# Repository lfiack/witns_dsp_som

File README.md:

# DSP System on Module from WITNS

## Make the project work
This project uses a submodule for the KiCAD library. To get it properly, use the `--recursive` option when cloning the repo :

```bash
git clone --recursive git@github.com:lfiack/witns_dsp_som
```

If you forgot the `--recursive` option (as I do quite often), you can type the following command :

```bash
git submodule update --init --recursive
```

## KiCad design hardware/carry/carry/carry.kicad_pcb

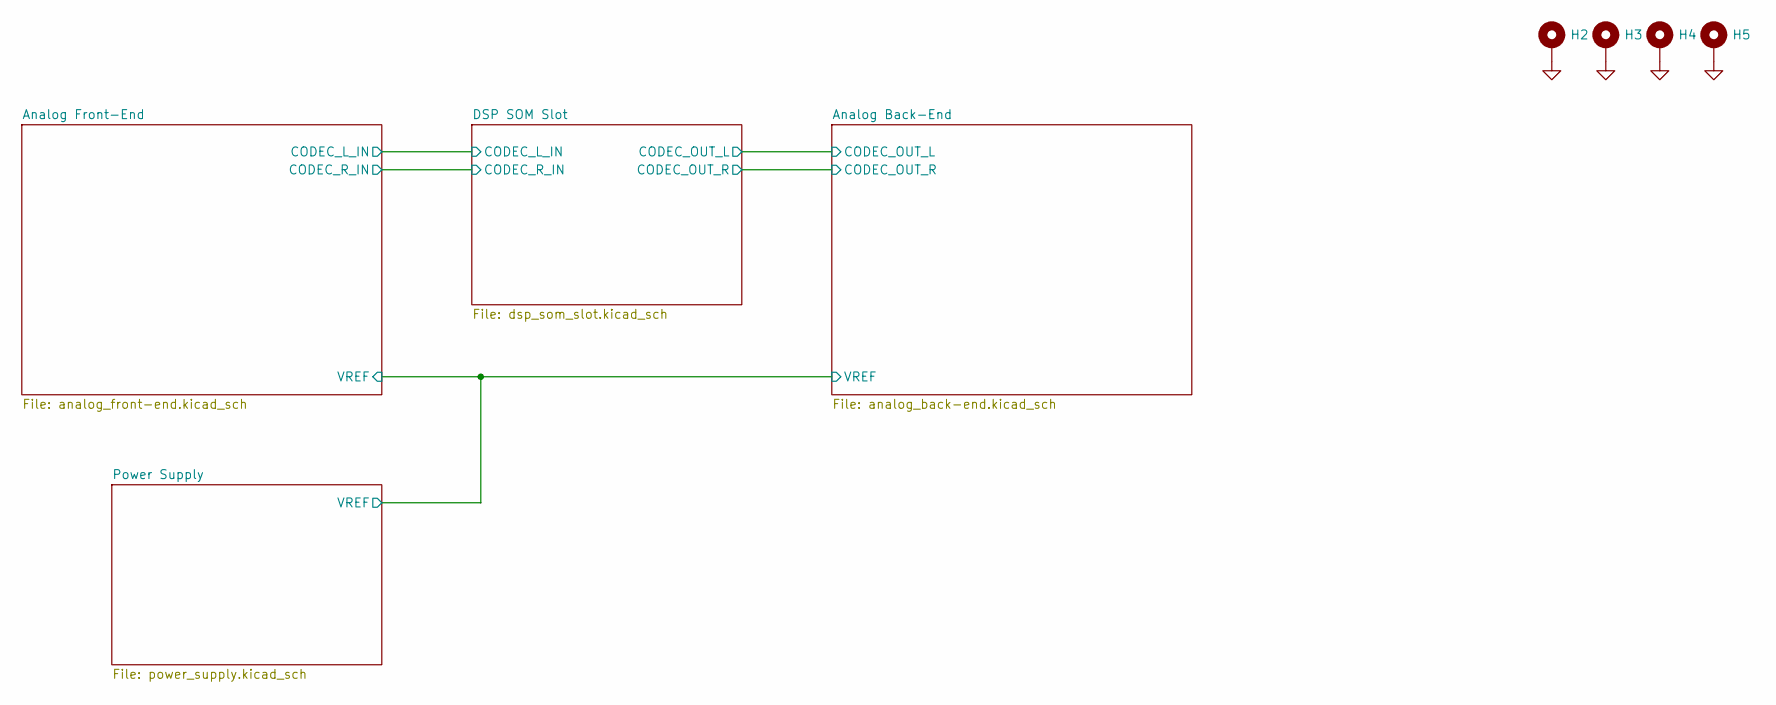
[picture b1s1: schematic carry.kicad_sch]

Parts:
H2, H3, H4, H5: MountingHole_Pad; MountingHole_3.2mm_M3_Pad_Via

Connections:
GND: H2.1, H3.1, H4.1, H5.1; also elsewhere on the board

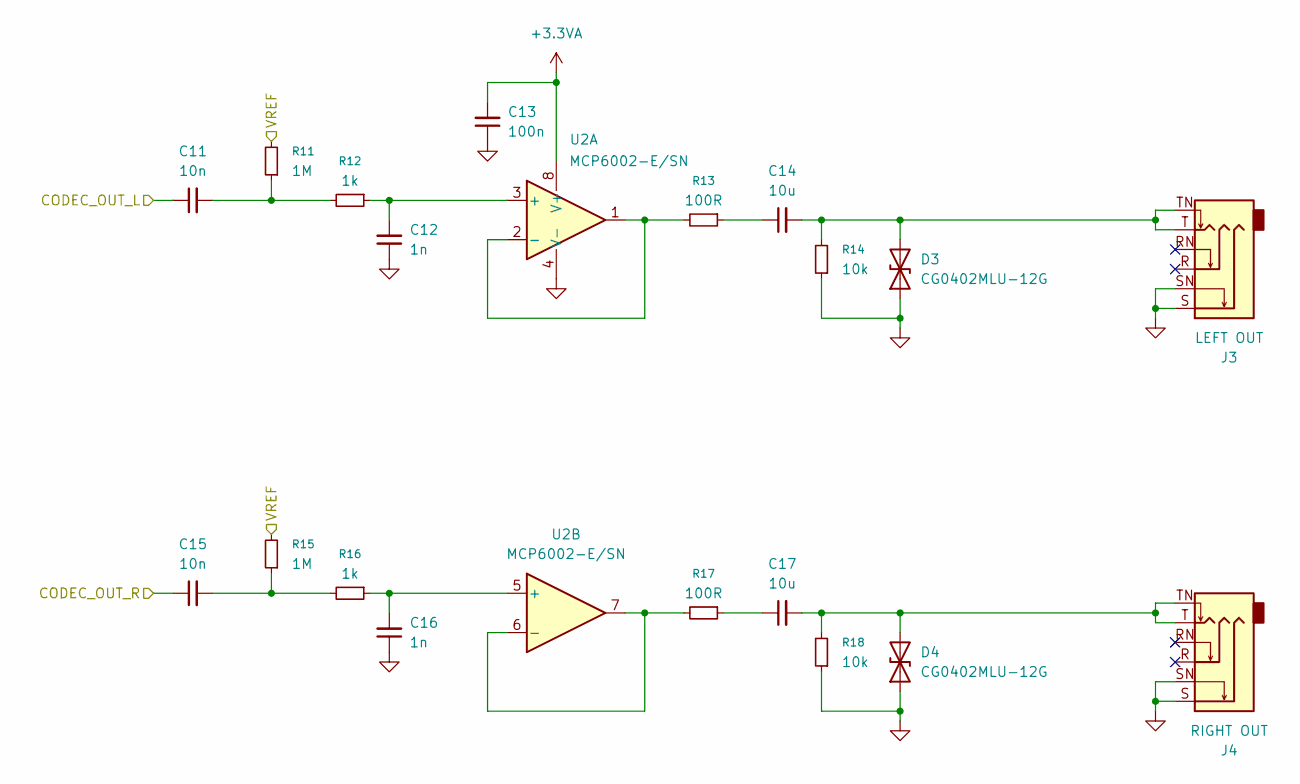
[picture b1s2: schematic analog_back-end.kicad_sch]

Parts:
C11, C15: 10n; C_0603_1608Metric
C12, C16: 1n; C_0603_1608Metric
C13: 100n; C_0603_1608Metric
C14, C17: 10u; C_0603_1608Metric
D3, D4: CG0402MLU-12G; D_0402_1005Metric
J3: LEFT OUT; Jack_6.35mm_Neutrik_NMJ6HCD3_Horizontal
J4: RIGHT OUT; Jack_6.35mm_Neutrik_NMJ6HCD3_Horizontal
R11, R15: 1M; R_0603_1608Metric
R12, R16: 1k; R_0603_1608Metric
R13, R17: 100R; R_0603_1608Metric
R14, R18: 10k; R_0603_1608Metric
U2: MCP6002-E/SN; SOIC-8_3.9x4.9mm_P1.27mm

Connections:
+3.3VA: C13.2, U2.8 (V+); also elsewhere on the board
/Analog Back-End/CODEC_OUT_L: C11.1; also elsewhere on the board
/Analog Back-End/CODEC_OUT_R: C15.1; also elsewhere on the board
/Analog Back-End/VREF: R11.2, R15.2; also elsewhere on the board
GND: C12.1, C13.1, C16.1, D3.1 (A1), D4.1 (A1), J3.S, J3.SN, J4.S, J4.SN, R14.1, R18.1, U2.4 (V-); also elsewhere on the board
unnamed: C11.2, R11.1, R12.2
unnamed: C14.1, R13.1
unnamed: C15.2, R15.1, R16.2
unnamed: C17.1, R17.1
unnamed: C14.2, D3.2 (A2), J3.T, J3.TN, R14.2
unnamed: C17.2, D4.2 (A2), J4.T, J4.TN, R18.2
unnamed: C12.2, R12.1, U2.3 (+)
unnamed: R13.2, U2.1, U2.2 (-)
unnamed: C16.2, R16.1, U2.5 (+)
unnamed: R17.2, U2.6 (-), U2.7

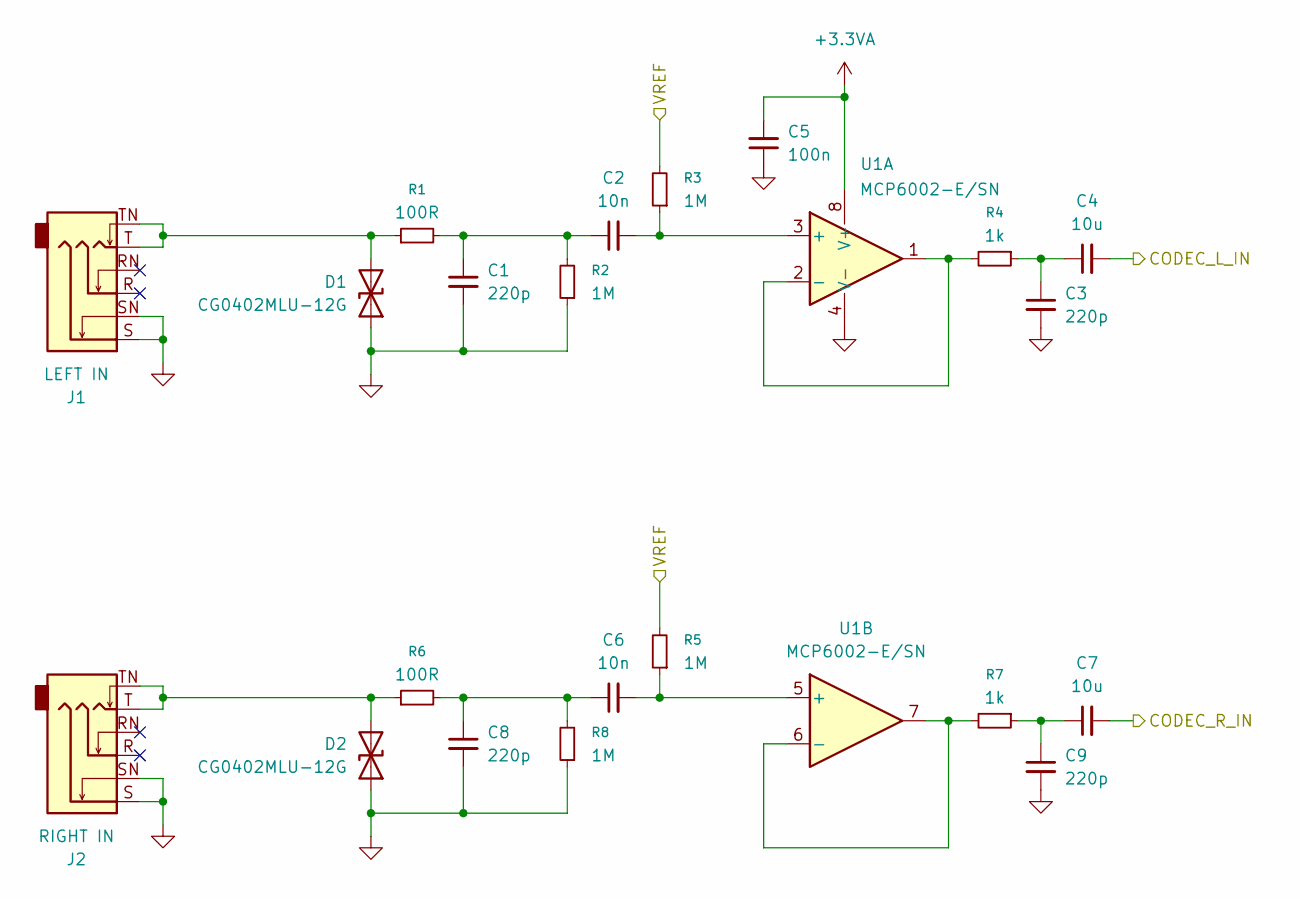
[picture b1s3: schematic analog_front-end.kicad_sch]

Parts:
C1, C3, C8, C9: 220p; C_0603_1608Metric
C2, C6: 10n; C_0603_1608Metric
C4, C7: 10u; C_0603_1608Metric
C5: 100n; C_0603_1608Metric
D1, D2: CG0402MLU-12G; D_0402_1005Metric
J1: LEFT IN; Jack_6.35mm_Neutrik_NMJ6HCD3_Horizontal
J2: RIGHT IN; Jack_6.35mm_Neutrik_NMJ6HCD3_Horizontal
R1, R6: 100R; R_0603_1608Metric
R2, R3, R5, R8: 1M; R_0603_1608Metric
R4, R7: 1k; R_0603_1608Metric
U1: MCP6002-E/SN; SOIC-8_3.9x4.9mm_P1.27mm

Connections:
+3.3VA: C5.2, U1.8 (V+); also elsewhere on the board
/Analog Back-End/VREF: R3.2, R5.2; also elsewhere on the board
/Analog Front-End/CODEC_L_IN: C4.2; also elsewhere on the board
/Analog Front-End/CODEC_R_IN: C7.2; also elsewhere on the board
GND: C1.2, C3.2, C5.1, C8.2, C9.2, D1.1 (A1), D2.1 (A1), J1.S, J1.SN, J2.S, J2.SN, R2.1, R8.1, U1.4 (V-); also elsewhere on the board
unnamed: C1.1, C2.1, R1.2, R2.2
unnamed: C3.1, C4.1, R4.1
unnamed: C6.1, C8.1, R6.2, R8.2
unnamed: C7.1, C9.1, R7.1
unnamed: D1.2 (A2), J1.T, J1.TN, R1.1
unnamed: D2.2 (A2), J2.T, J2.TN, R6.1
unnamed: C2.2, R3.1, U1.3 (+)
unnamed: R4.2, U1.1, U1.2 (-)
unnamed: C6.2, R5.1, U1.5 (+)
unnamed: R7.2, U1.6 (-), U1.7

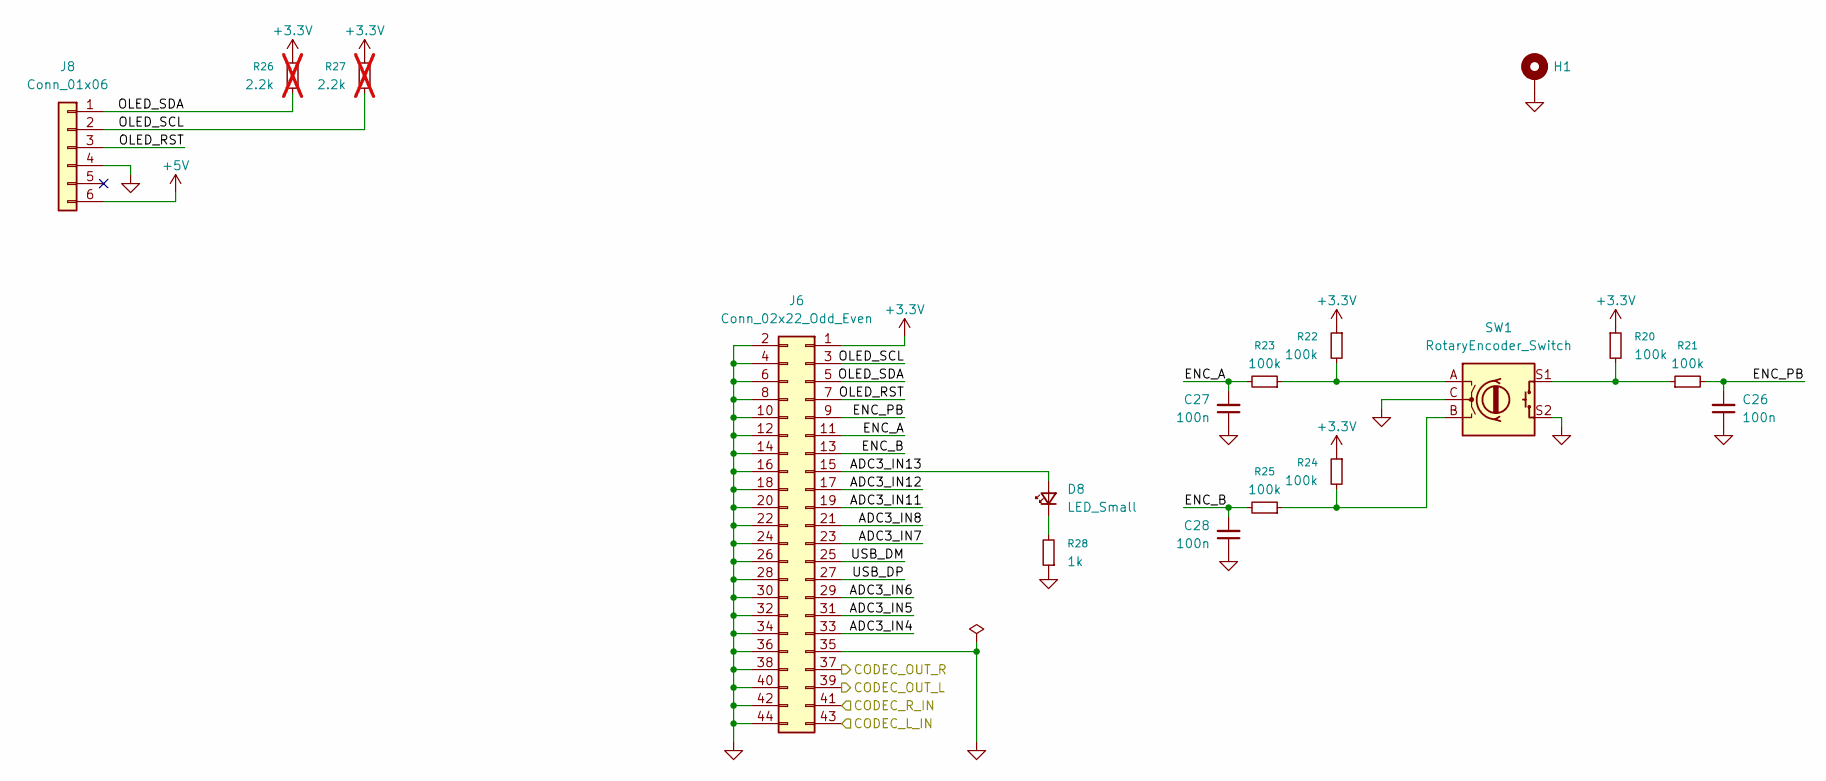
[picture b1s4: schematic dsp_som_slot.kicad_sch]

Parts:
C26, C27, C28: 100n; C_0603_1608Metric
D8: LED_Small; LED_0603_1608Metric
H1: MountingHole_Pad; MountingHole_3.2mm_M3_Pad_Via
J6: Conn_02x22_Odd_Even; PinSocket_2x22_P2.54mm_Vertical
J8: Conn_01x06; PinSocket_1x06_P2.54mm_Vertical
R20, R21, R22, R23, R24, R25: 100k; R_0603_1608Metric
R26, R27: 2.2k; R_0603_1608Metric; not fitted
R28: 1k; R_0603_1608Metric
SW1: RotaryEncoder_Switch; RotaryEncoder_Alps_EC12E-Switch_Vertical_H20mm_CircularMoun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

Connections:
+3.3V: J6.1, R20.1, R22.1, R24.1, R26.1, R27.1; also elsewhere on the board
+5V: J8.6; also elsewhere on the board
/Analog Back-End/CODEC_OUT_L: J6.39; also elsewhere on the board
/Analog Back-End/CODEC_OUT_R: J6.37; also elsewhere on the board
/Analog Front-End/CODEC_L_IN: J6.43; also elsewhere on the board
/Analog Front-End/CODEC_R_IN: J6.41; also elsewhere on the board
/DSP SOM Slot/ADC3_IN4: J6.33
/DSP SOM Slot/ADC3_IN5: J6.31
/DSP SOM Slot/ADC3_IN6: J6.29
/DSP SOM Slot/ADC3_IN7: J6.23
/DSP SOM Slot/ADC3_IN8: J6.21
/DSP SOM Slot/ADC3_IN11: J6.19
/DSP SOM Slot/ADC3_IN12: J6.17
/DSP SOM Slot/ADC3_IN13: D8.2 (A), J6.15
/DSP SOM Slot/ENC_A: C27.2, J6.11, R23.2
/DSP SOM Slot/ENC_B: C28.2, J6.13, R25.2
/DSP SOM Slot/ENC_PB: C26.2, J6.9, R21.2
/DSP SOM Slot/OLED_RST: J6.7, J8.3
/DSP SOM Slot/OLED_SCL: J6.3, J8.2, R27.2
/DSP SOM Slot/OLED_SDA: J6.5, J8.1, R26.2
/DSP SOM Slot/USB_DM: J6.25
/DSP SOM Slot/USB_DP: J6.27
GND: C26.1, C27.1, C28.1, H1.1, J6.2, J6.4, J6.6, J6.8, J6.10, J6.12, J6.14, J6.16, J6.18, J6.20, J6.22, J6.24, J6.26, J6.28, J6.30, J6.32, J6.34, J6.35, J6.36, J6.38, J6.40, J6.42, J6.44, J8.4, R28.1, SW1.C, SW1.S2; also elsewhere on the board
unnamed: D8.1 (K), R28.2
unnamed: R20.2, R21.1, SW1.S1
unnamed: R22.2, R23.1, SW1.A
unnamed: R24.2, R25.1, SW1.B

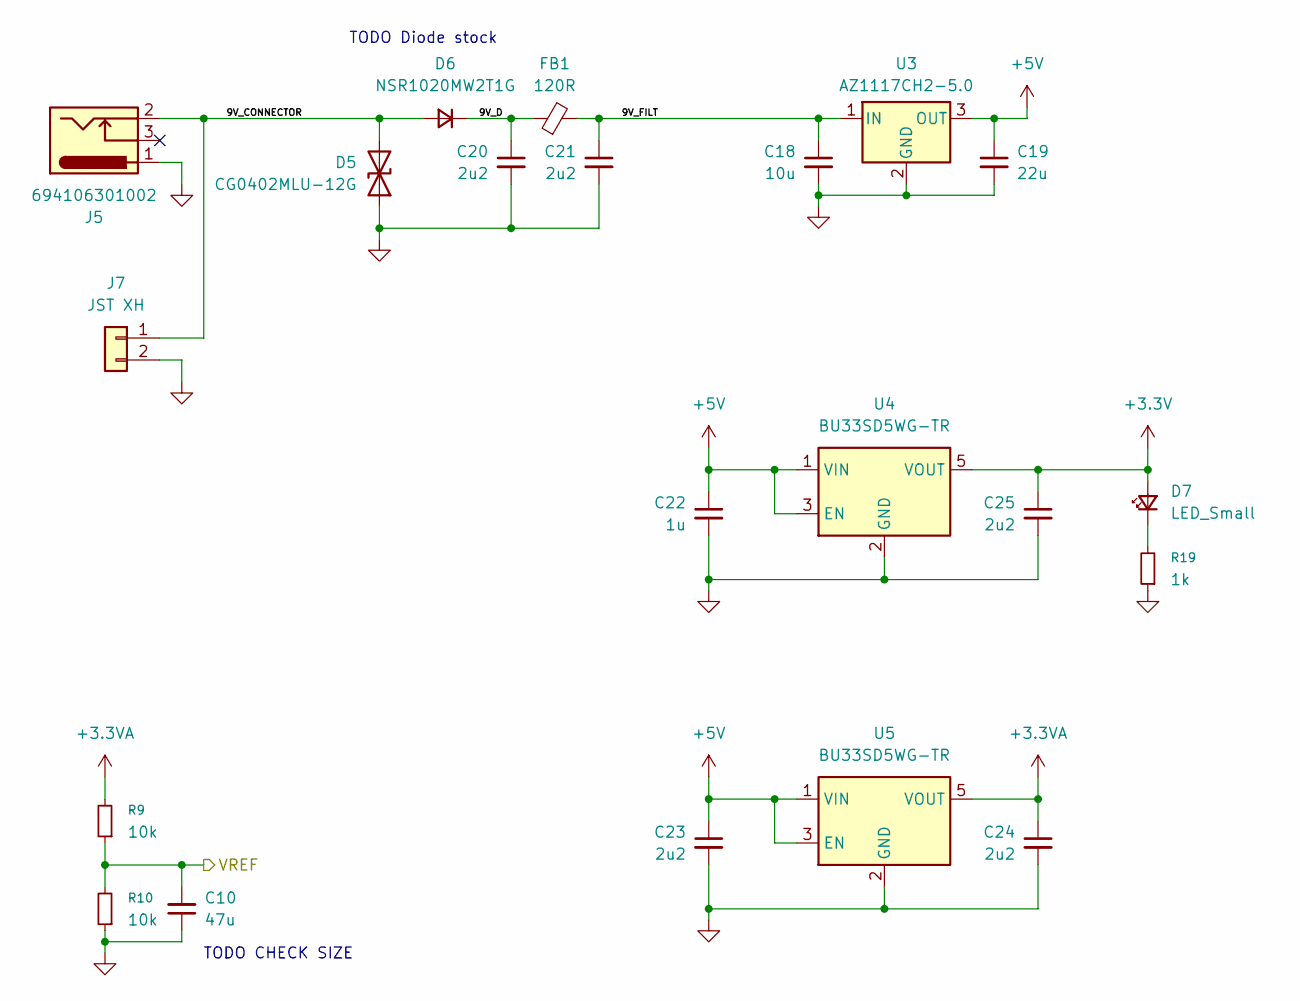
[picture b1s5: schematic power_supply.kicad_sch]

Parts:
C10: 47u; C_0603_1608Metric
C18: 10u; C_0805_2012Metric
C19: 22u; C_0805_2012Metric
C20, C21, C23, C24, C25: 2u2; C_0603_1608Metric
C22: 1u; C_0603_1608Metric
D5: CG0402MLU-12G; D_0402_1005Metric
D6: NSR1020MW2T1G; D_SOD-323
D7: LED_Small; LED_0603_1608Metric
FB1: 120R; L_0603_1608Metric
J5: 694106301002; BarrelJack_Wuerth_6941xx301002
J7: JST XH; JST_XH_B2B-XH-A_1x02_P2.50mm_Vertical
R9, R10: 10k; R_0603_1608Metric
R19: 1k; R_0603_1608Metric
U3: AZ1117CH2-5.0; SOT-223-3_TabPin2
U4, U5: BU33SD5WG-TR; SOT-23-5

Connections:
+3.3V: C25.1, D7.2 (A), U4.5 (VOUT); also elsewhere on the board
+3.3VA: C24.1, R9.2, U5.5 (VOUT); also elsewhere on the board
+5V: C19.1, C22.1, C23.1, U3.3 (OUT), U4.1 (VIN), U4.3 (EN), U5.1 (VIN), U5.3 (EN); also elsewhere on the board
/Analog Back-End/VREF: C10.2, R9.1, R10.2; also elsewhere on the board
/Power Supply/9V_CONNECTOR: D5.2 (A2), D6.2 (A), J5.2, J7.1
/Power Supply/9V_D: C20.1, D6.1 (K), FB1.1
/Power Supply/9V_FILT: C18.1, C21.1, FB1.2, U3.1 (IN)
GND: C10.1, C18.2, C19.2, C20.2, C21.2, C22.2, C23.2, C24.2, C25.2, D5.1 (A1), J5.1, J7.2, R10.1, R19.1, U3.2 (GND), U4.2 (GND), U5.2 (GND); also elsewhere on the board
unnamed: D7.1 (K), R19.2

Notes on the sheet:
TODO Diode stock
TODO CHECK SIZE

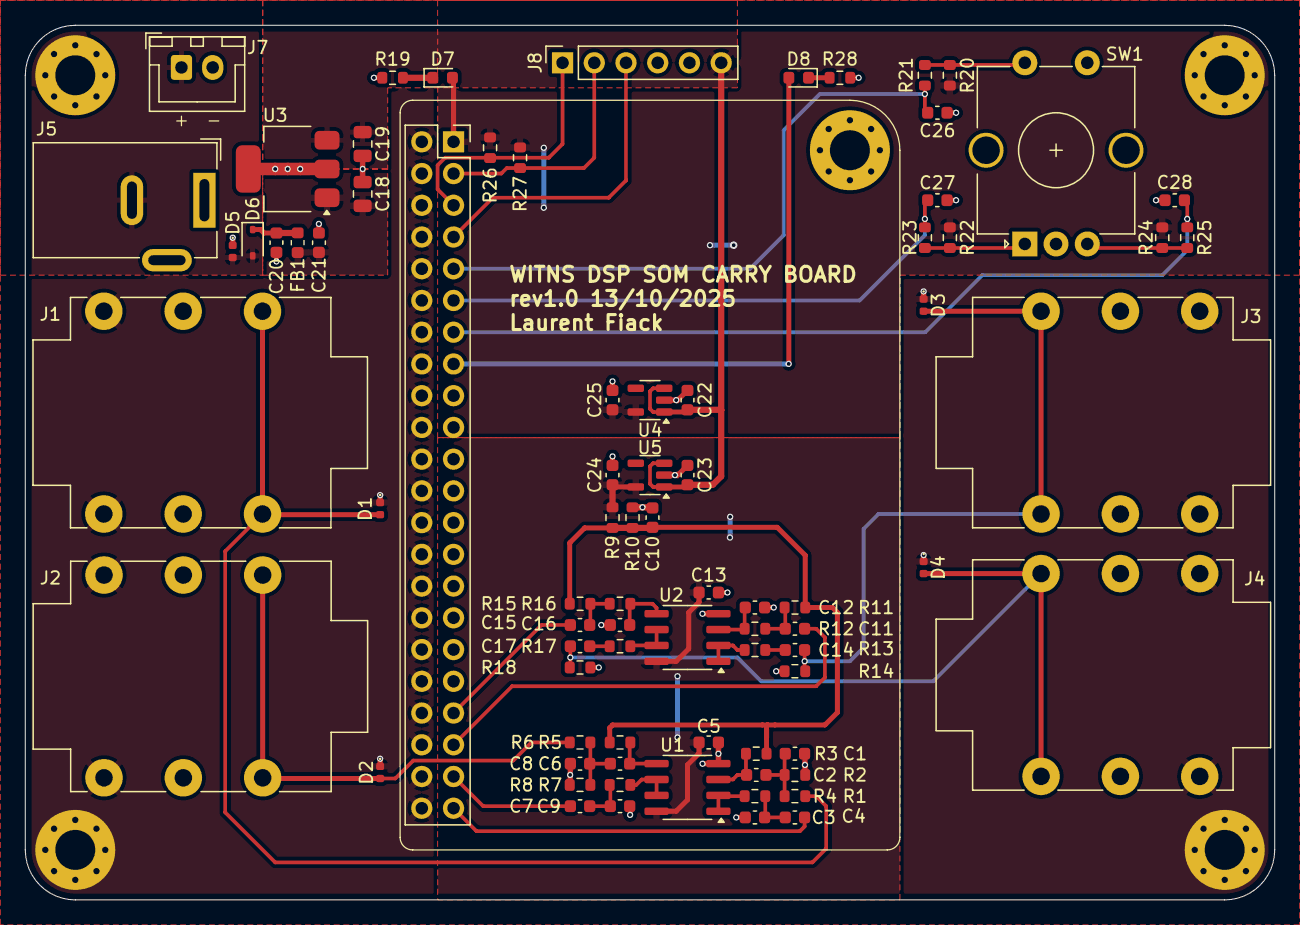
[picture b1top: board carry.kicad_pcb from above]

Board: 2 copper layers, 100.0 x 70.0 mm, 84 parts (0 on the bottom side), 44 nets.

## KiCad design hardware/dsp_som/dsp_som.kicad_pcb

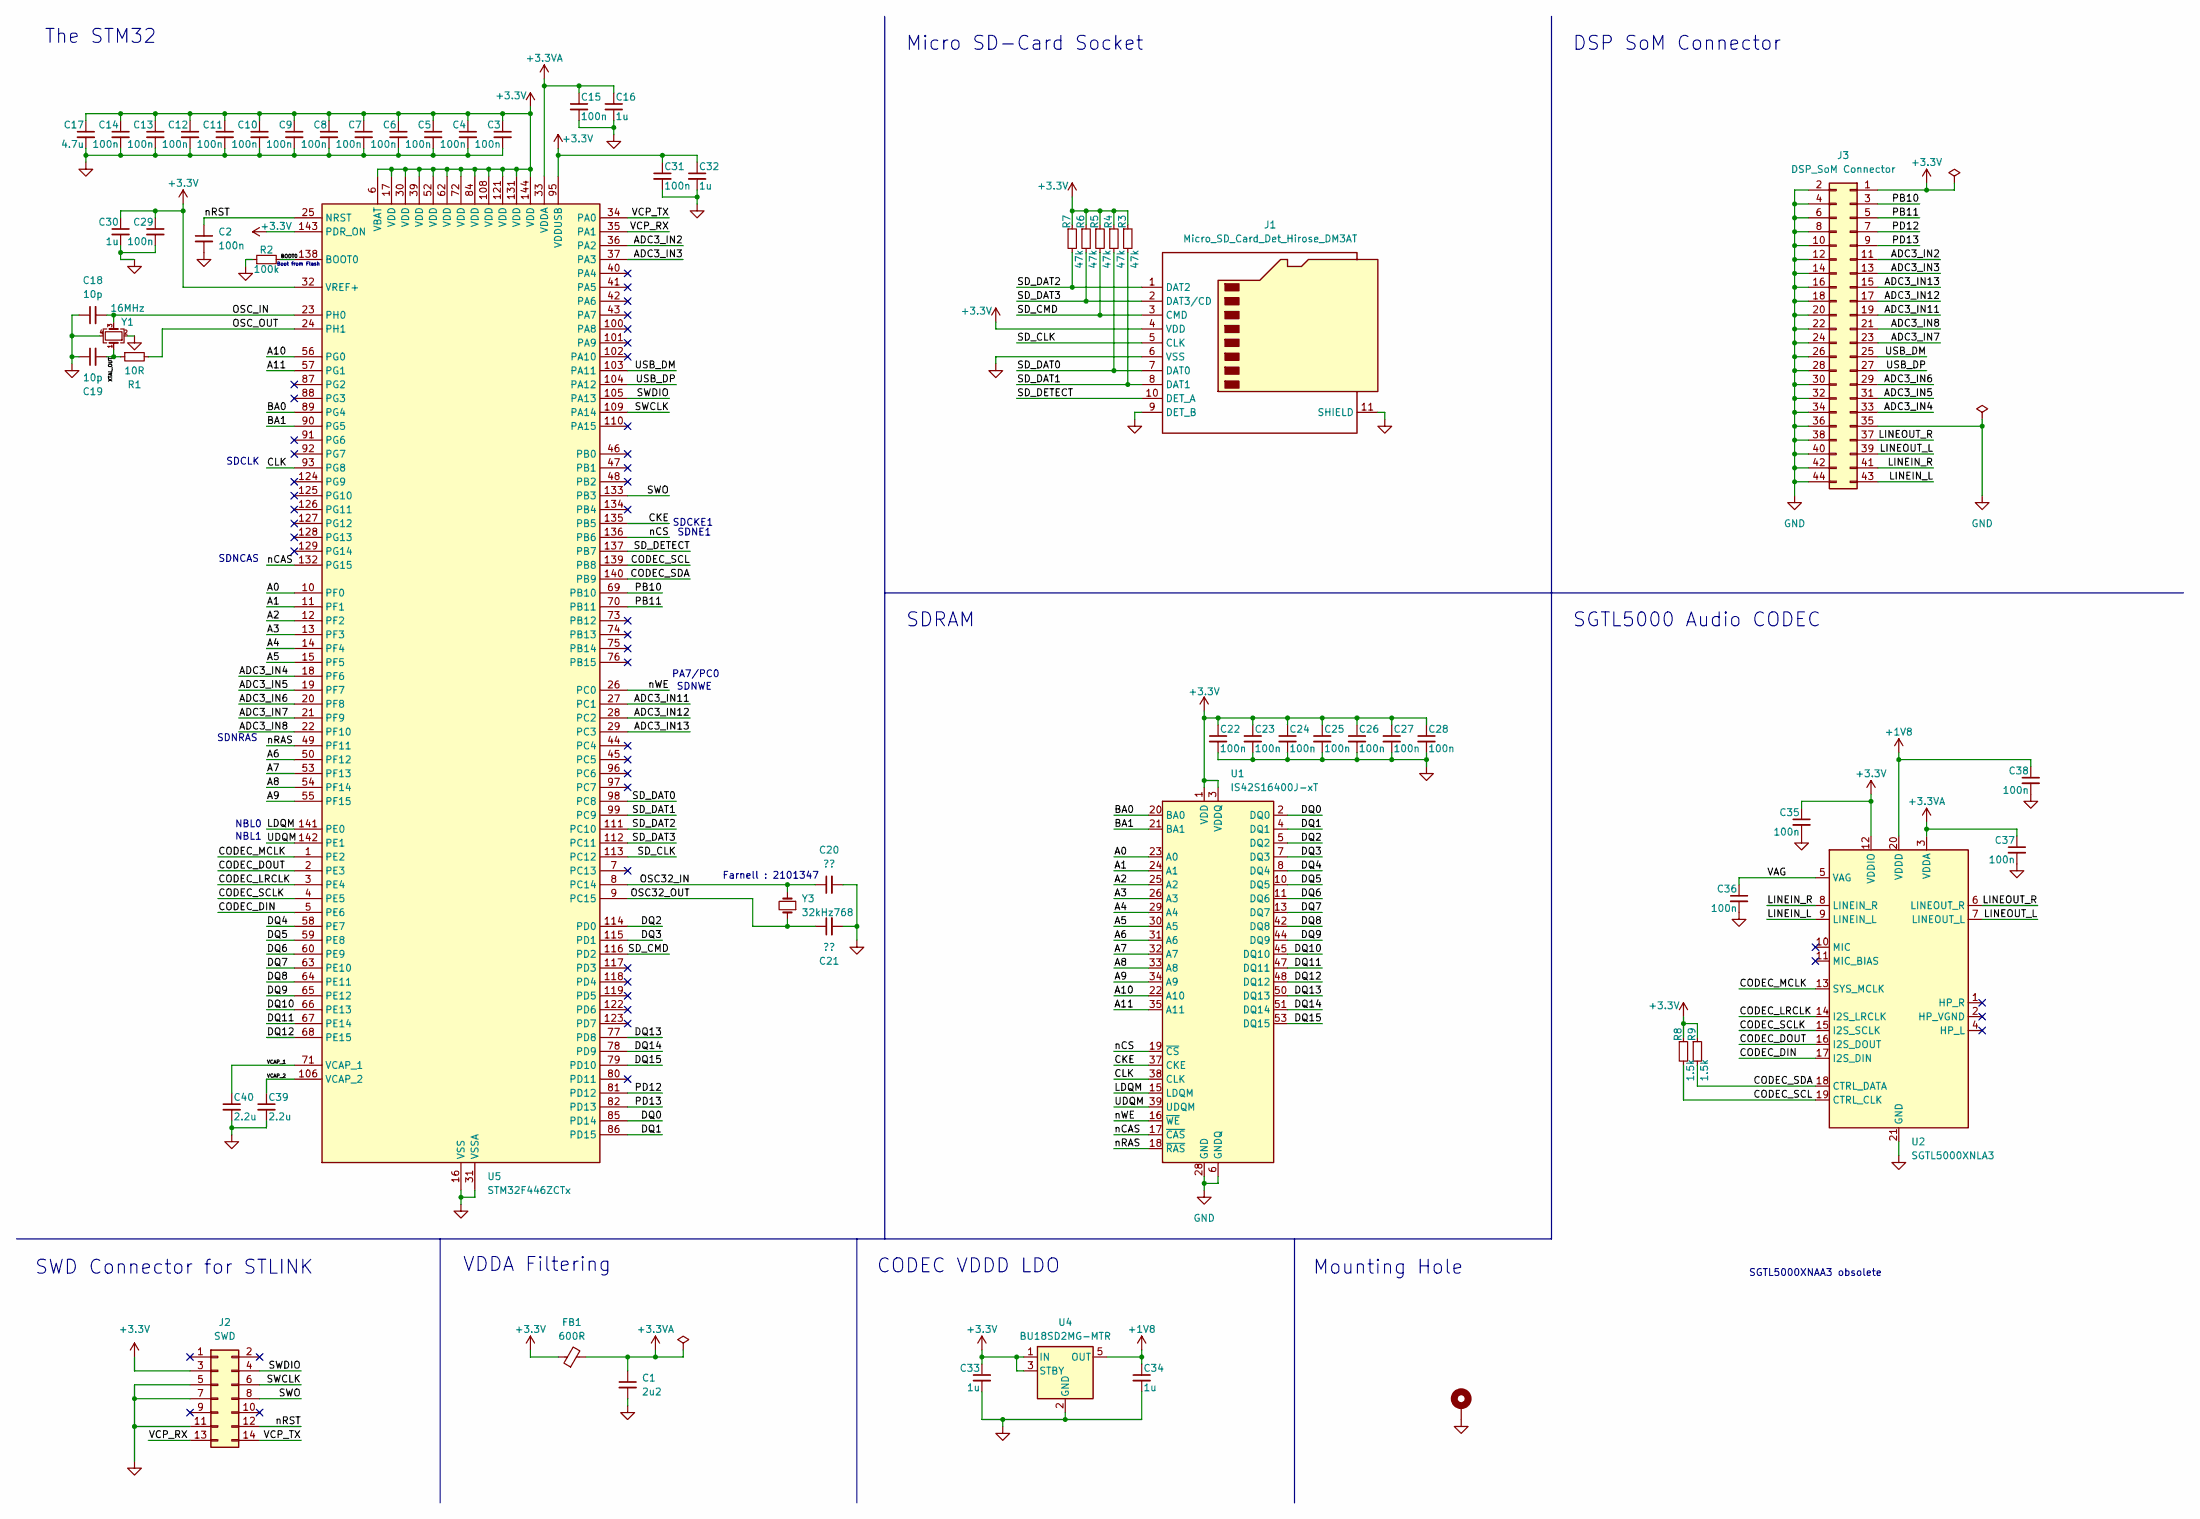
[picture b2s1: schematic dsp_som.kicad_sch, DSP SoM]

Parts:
C1: 2u2; C_0603_1608Metric
C2, C3, C4, C5, C6, C7, C8, C9, C10, C11, C12, C13, C14, C15, C22, C23, C24, C25, C26, C27, C28, C29, C31, C35, C36, C37, C38: 100n; C_0402_1005Metric
C16, C30, C32, C33, C34: 1u; C_0603_1608Metric
C17: 4.7u; C_0603_1608Metric
C18, C19: 10p; C_0402_1005Metric
C20, C21: ??; C_0402_1005Metric
C39, C40: 2.2u; C_0603_1608Metric
FB1: 600R; L_0603_1608Metric
H1: MountingHole_Pad; MountingHole_3.2mm_M3_Pad_Via
J1: Micro_SD_Card_Det_Hirose_DM3AT; microSD_HC_Hirose_DM3AT-SF-PEJM5
J2: SWD; PinHeader_2x07_P1.27mm_Vertical_SMD
J3: DSP_SoM Connector; PinHeader_2x22_P2.54mm_Vertical
R1: 10R; R_0402_1005Metric
R2: 100k; R_0402_1005Metric
R3, R4, R5, R6, R7: 47k; R_0402_1005Metric
R8, R9: 1.5k; R_0402_1005Metric
U1: IS42S16400J-xT; TSOP-II-54_22.2x10.16mm_P0.8mm
U2: SGTL5000XNLA3; QFN-20-1EP_3x3mm_P0.4mm_EP1.65x1.65mm
U4: BU18SD2MG-MTR; SOT-23-5
U5: STM32F446ZCTx; LQFP-144_20x20mm_P0.5mm
Y1: 16MHz; Crystal_SMD_EuroQuartz_MT-4Pin_3.2x2.5mm; Farnell 2853935
Y3: 32kHz768; Crystal_SMD_3215-2Pin_3.2x1.5mm

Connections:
+1V8: C34.1, C38.1, U2.20 (VDDD), U4.5 (OUT)
+3.3V: C3.1, C4.1, C5.1, C6.1, C7.1, C8.1, C9.1, C10.1, C11.1, C12.1, C13.1, C14.1, C17.1, C22.1, C23.1, C24.1, C25.1, C26.1, C27.1, C28.1, C29.1, C30.1, C31.1, C32.1, C33.1, C35.1, FB1.1, J1.4 (VDD), J2.3, J3.1, R3.1, R4.1, R5.1, R6.1, R7.1, R8.1, R9.1, U1.1 (VDD), U1.3 (VDDQ), U1.9 (VDDQ), U1.14 (VDD), U1.27 (VDD), U1.43 (VDDQ), U1.49 (VDDQ), U2.12 (VDDIO), U4.1 (IN), U4.3 (STBY), U5.6 (VBAT), U5.17 (VDD), U5.30 (VDD), U5.32 (VREF+), U5.39 (VDD), U5.52 (VDD), U5.62 (VDD), U5.72 (VDD), U5.84 (VDD), U5.95 (VDDUSB), U5.108 (VDD), U5.121 (VDD), U5.131 (VDD), U5.143 (PDR_ON), U5.144 (VDD)
+3.3VA: C1.1, C15.1, C16.1, C37.1, FB1.2, U2.3 (VDDA), U5.33 (VDDA)
/A0: U1.23 (A0), U5.10 (PF0)
/A1: U1.24 (A1), U5.11 (PF1)
/A2: U1.25 (A2), U5.12 (PF2)
/A3: U1.26 (A3), U5.13 (PF3)
/A4: U1.29 (A4), U5.14 (PF4)
/A5: U1.30 (A5), U5.15 (PF5)
/A6: U1.31 (A6), U5.50 (PF12)
/A7: U1.32 (A7), U5.53 (PF13)
/A8: U1.33 (A8), U5.54 (PF14)
/A9: U1.34 (A9), U5.55 (PF15)
/A10: U1.22 (A10), U5.56 (PG0)
/A11: U1.35 (A11), U5.57 (PG1)
/ADC3_IN2: J3.11, U5.36 (PA2)
/ADC3_IN3: J3.13, U5.37 (PA3)
/ADC3_IN4: J3.33, U5.18 (PF6)
/ADC3_IN5: J3.31, U5.19 (PF7)
/ADC3_IN6: J3.29, U5.20 (PF8)
/ADC3_IN7: J3.23, U5.21 (PF9)
/ADC3_IN8: J3.21, U5.22 (PF10)
/ADC3_IN11: J3.19, U5.27 (PC1)
/ADC3_IN12: J3.17, U5.28 (PC2)
/ADC3_IN13: J3.15, U5.29 (PC3)
/BA0: U1.20 (BA0), U5.89 (PG4)
/BA1: U1.21 (BA1), U5.90 (PG5)
/BOOT0: R2.2, U5.138 (BOOT0)
/CKE: U1.37 (CKE), U5.135 (PB5)
/CLK: U1.38 (CLK), U5.93 (PG8)
/CODEC_DIN: U2.17 (I2S_DIN), U5.5 (PE6)
/CODEC_DOUT: U2.16 (I2S_DOUT), U5.2 (PE3)
/CODEC_LRCLK: U2.14 (I2S_LRCLK), U5.3 (PE4)
/CODEC_MCLK: U2.13 (SYS_MCLK), U5.1 (PE2)
/CODEC_SCL: R8.2, U2.19 (CTRL_CLK), U5.139 (PB8)
/CODEC_SCLK: U2.15 (I2S_SCLK), U5.4 (PE5)
/CODEC_SDA: R9.2, U2.18 (CTRL_DATA), U5.140 (PB9)
/DQ0: U1.2 (DQ0), U5.85 (PD14)
/DQ1: U1.4 (DQ1), U5.86 (PD15)
/DQ2: U1.5 (DQ2), U5.114 (PD0)
/DQ3: U1.7 (DQ3), U5.115 (PD1)
/DQ4: U1.8 (DQ4), U5.58 (PE7)
/DQ5: U1.10 (DQ5), U5.59 (PE8)
/DQ6: U1.11 (DQ6), U5.60 (PE9)
/DQ7: U1.13 (DQ7), U5.63 (PE10)
/DQ8: U1.42 (DQ8), U5.64 (PE11)
/DQ9: U1.44 (DQ9), U5.65 (PE12)
/DQ10: U1.45 (DQ10), U5.66 (PE13)
/DQ11: U1.47 (DQ11), U5.67 (PE14)
/DQ12: U1.48 (DQ12), U5.68 (PE15)
/DQ13: U1.50 (DQ13), U5.77 (PD8)
/DQ14: U1.51 (DQ14), U5.78 (PD9)
/DQ15: U1.53 (DQ15), U5.79 (PD10)
/LDQM: U1.15 (LDQM), U5.141 (PE0)
/LINEIN_L: J3.43, U2.9 (LINEIN_L)
/LINEIN_R: J3.41, U2.8 (LINEIN_R)
/LINEOUT_L: J3.39, U2.7 (LINEOUT_L)
/LINEOUT_R: J3.37, U2.6 (LINEOUT_R)
/OSC32_IN: C20.1, U5.8 (PC14), Y3.2
/OSC32_OUT: C21.1, U5.9 (PC15), Y3.1
/OSC_IN: C18.2, U5.23 (PH0), Y1.3
/OSC_OUT: R1.2, U5.24 (PH1)
/PB10: J3.3, U5.69 (PB10)
/PB11: J3.5, U5.70 (PB11)
/PD12: J3.7, U5.81 (PD12)
/PD13: J3.9, U5.82 (PD13)
/SD_CLK: J1.5 (CLK), U5.113 (PC12)
/SD_CMD: J1.3 (CMD), R5.2, U5.116 (PD2)
/SD_DAT0: J1.7 (DAT0), R4.2, U5.98 (PC8)
/SD_DAT1: J1.8 (DAT1), R3.2, U5.99 (PC9)
/SD_DAT2: J1.1 (DAT2), R7.2, U5.111 (PC10)
/SD_DAT3: J1.2 (DAT3/CD), R6.2, U5.112 (PC11)
/SD_DETECT: J1.10 (DET_A), U5.137 (PB7)
/SWCLK: J2.6, U5.109 (PA14)
/SWDIO: J2.4, U5.105 (PA13)
/SWO: J2.8, U5.133 (PB3)
/UDQM: U1.39 (UDQM), U5.142 (PE1)
/USB_DM: J3.25, U5.103 (PA11)
/USB_DP: J3.27, U5.104 (PA12)
/VAG: C36.1, U2.5 (VAG)
/VCAP_1: C40.1, U5.71 (VCAP_1)
/VCAP_2: C39.1, U5.106 (VCAP_2)
/VCP_RX: J2.13, U5.35 (PA1)
/VCP_TX: J2.14, U5.34 (PA0)
/XTAL_OUT: C19.2, R1.1, Y1.1
/nCAS: U1.17 (~CAS), U5.132 (PG15)
/nCS: U1.19 (~CS), U5.136 (PB6)
/nRAS: U1.18 (~RAS), U5.49 (PF11)
/nRST: C2.1, J2.12, U5.25 (NRST)
/nWE: U1.16 (~WE), U5.26 (PC0)
GND: C1.2, C2.2, C3.2, C4.2, C5.2, C6.2, C7.2, C8.2, C9.2, C10.2, C11.2, C12.2, C13.2, C14.2, C15.2, C16.2, C17.2, C18.1, C19.1, C20.2, C21.2, C22.2, C23.2, C24.2, C25.2, C26.2, C27.2, C28.2, C29.2, C30.2, C31.2, C32.2, C33.2, C34.2, C35.2, C36.2, C37.2, C38.2, C39.2, C40.2, H1.1, J1.6 (VSS), J1.9 (DET_B), J1.11 (SHIELD), J2.5, J2.7, J2.11, J3.2, J3.4, J3.6, J3.8, J3.10, J3.12, J3.14, J3.16, J3.18, J3.20, J3.22, J3.24, J3.26, J3.28, J3.30, J3.32, J3.34, J3.35, J3.36, J3.38, J3.40, J3.42, J3.44, R2.1, U1.6 (GNDQ), U1.12 (GNDQ), U1.28 (GND), U1.41 (GND), U1.46 (GNDQ), U1.52 (GNDQ), U1.54 (GND), U2.21 (GND), U4.2 (GND)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

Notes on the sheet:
Mounting Hole
NBL0
SDCLK
CODEC VDDD LDO
SGTL5000 Audio CODEC
Boot from Flash
Farnell : 2101347
SGTL5000XNAA3 obsolete
Micro SD-Card Socket
NBL1
PA7/PC0
SDNCAS
SDNRAS
SDRAM
SDNWE
VDDA Filtering
The STM32
SDNE1
SWD Connector for STLINK
DSP SoM Connector
SDCKE1

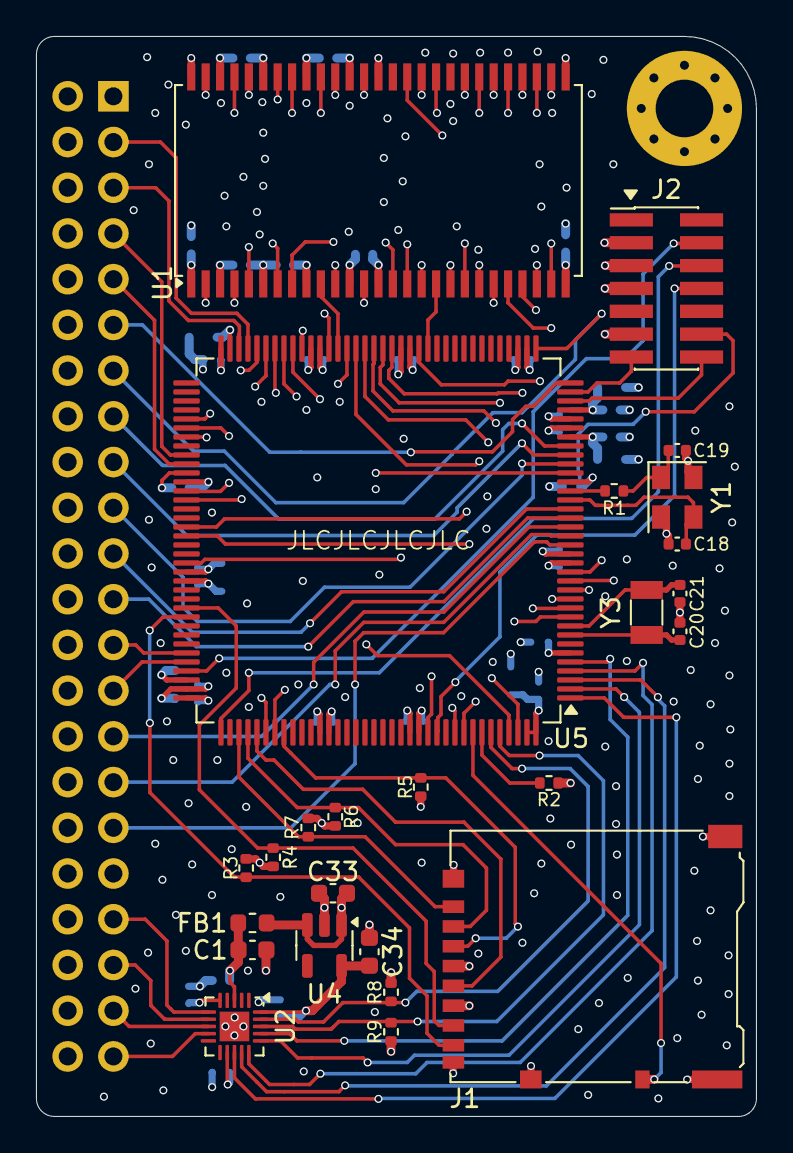
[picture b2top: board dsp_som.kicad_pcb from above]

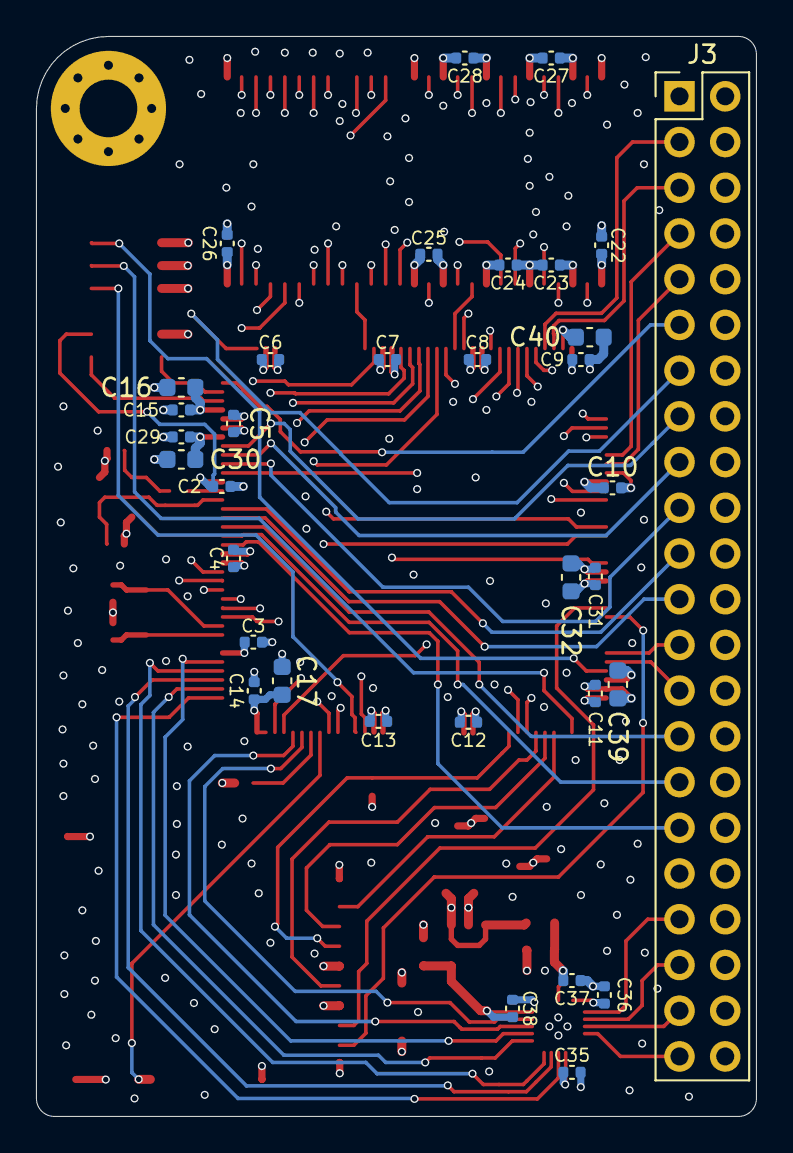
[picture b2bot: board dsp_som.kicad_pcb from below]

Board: 6 copper layers, 40.0 x 60.0 mm, 60 parts (34 on the bottom side), 91 nets.

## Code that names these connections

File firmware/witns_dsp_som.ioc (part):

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Mcu.Name=STM32F446Z(C-E)Tx
Mcu.Package=LQFP144
Mcu.UserName=STM32F446ZCTx
PA0-WKUP.GPIOParameters=GPIO_Label
PA0-WKUP.GPIO_Label=VCP_TX
PA0-WKUP.Mode=Asynchronous
PA0-WKUP.Signal=UART4_TX
PA1.GPIOParameters=GPIO_Label
PA1.GPIO_Label=VCP_RX
PA1.Mode=Asynchronous
PA1.Signal=UART4_RX
PA11.Mode=Device_Only
PA11.Signal=USB_OTG_FS_DM
PA12.Mode=Device_Only
PA12.Signal=USB_OTG_FS_DP
PA13.Mode=Trace_Asynchronous_SW
PA13.Signal=SYS_JTMS-SWDIO
PA14.Mode=Trace_Asynchronous_SW
PA14.Signal=SYS_JTCK-SWCLK
PA2.GPIOParameters=GPIO_Label
PA2.GPIO_Label=ENC_A
PA2.Signal=GPXTI2
PA3.GPIOParameters=GPIO_Label
PA3.GPIO_Label=ENC_B
PA3.Signal=GPXTI3
PB10.Signal=I2C2_SCL
PB11.Signal=I2C2_SDA
PB3.Mode=Trace_Asynchronous_SW
PB3.Signal=SYS_JTDO-SWO
PB5.Mode=SdramChipSelect2_1
PB5.Signal=FMC_SDCKE1
PB6.Mode=SdramChipSelect2_1
PB6.Signal=FMC_SDNE1
PB7.GPIOParameters=GPIO_Label
PB7.GPIO_Label=SD_DETECT
PB7.Signal=GPIO_Output
PB8.Mode=I2C
PB8.Signal=I2C1_SCL
PB9.Mode=I2C
PB9.Signal=I2C1_SDA
PC0.Signal=FMC_SDNWE
PC1.Signal=ADCx_IN11
PC10.Mode=SD_4_bits_Wide_bus
PC10.Signal=SDIO_D2
PC11.Mode=SD_4_bits_Wide_bus
PC11.Signal=SDIO_D3
PC12.Mode=SD_4_bits_Wide_bus
PC12.Signal=SDIO_CK
PC14-OSC32_IN.Mode=LSE-External-Oscillator
PC14-OSC32_IN.Signal=RCC_OSC32_IN
PC15-OSC32_OUT.Mode=LSE-External-Oscillator
PC15-OSC32_OUT.Signal=RCC_OSC32_OUT
PC2.Signal=ADCx_IN12
PC3.Signal=ADCx_IN13
PC8.Mode=SD_4_bits_Wide_bus
PC8.Signal=SDIO_D0
PC9.Mode=SD_4_bits_Wide_bus
PC9.Signal=SDIO_D1
PD0.Signal=FMC_D2_DA2
PD1.Signal=FMC_D3_DA3
PD10.Signal=FMC_D15_DA15
PD12.GPIOParameters=GPIO_Label
PD12.GPIO_Label=OLED_RESET
PD12.Signal=GPIO_Output
PD13.GPIOParameters=GPIO_Label
PD13.GPIO_Label=ENC_PB
PD13.Signal=GPXTI13
PD14.Signal=FMC_D0_DA0
PD15.Signal=FMC_D1_DA1
PD2.Mode=SD_4_bits_Wide_bus
PD2.Signal=SDIO_CMD
PD8.Signal=FMC_D13_DA13
PD9.Signal=FMC_D14_DA14
PE0.Signal=FMC_NBL0
PE1.Signal=FMC_NBL1
PE10.Signal=FMC_D7_DA7
PE11.Signal=FMC_D8_DA8
PE12.Signal=FMC_D9_DA9
PE13.Signal=FMC_D10_DA10
PE14.Signal=FMC_D11_DA11
PE15.Signal=FMC_D12_DA12
PE2.Mode=SAI_A_MasterWithClock
PE2.Signal=SAI1_MCLK_A
PE3.Mode=SAI_B_SyncSlave
PE3.Signal=SAI1_SD_B
PE4.Mode=SAI_A_MasterWithClock
PE4.Signal=SAI1_FS_A
PE5.Mode=SAI_A_MasterWithClock
PE5.Signal=SAI1_SCK_A
PE6.Mode=SAI_A_MasterWithClock
PE6.Signal=SAI1_SD_A
PE7.Signal=FMC_D4_DA4
PE8.Signal=FMC_D5_DA5
PE9.Signal=FMC_D6_DA6
PF0.Signal=FMC_A0
PF1.Signal=FMC_A1
PF10.Mode=IN8
PF10.Signal=ADC3_IN8
PF11.Signal=FMC_SDNRAS
PF12.Signal=FMC_A6
PF13.Signal=FMC_A7
PF14.Signal=FMC_A8
PF15.Signal=FMC_A9
PF2.Signal=FMC_A2
PF3.Signal=FMC_A3
PF4.Signal=FMC_A4
PF5.Signal=FMC_A5
PF6.Mode=IN4
PF6.Signal=ADC3_IN4
PF7.Mode=IN5
PF7.Signal=ADC3_IN5
PF8.Mode=IN6
PF8.Signal=ADC3_IN6
PF9.Mode=IN7
PF9.Signal=ADC3_IN7
PG0.Signal=FMC_A10
PG1.Signal=FMC_A11
PG15.Signal=FMC_SDNCAS
PG4.Signal=FMC_A14_BA0
PG5.Signal=FMC_A15_BA1
PG8.Signal=FMC_SDCLK
PH0-OSC_IN.Mode=HSE-External-Oscillator
PH0-OSC_IN.Signal=RCC_OSC_IN
PH1-OSC_OUT.Mode=HSE-External-Oscillator
PH1-OSC_OUT.Signal=RCC_OSC_OUT
RCC.HSE_VALUE=16000000
RCC.SYSCLKFreq_VALUE=180000000
RCC.SYSCLKSource=RCC_SYSCLKSOURCE_PLLCLK
board=custom

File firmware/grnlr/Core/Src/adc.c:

/* USER CODE BEGIN Header */
/**
  ******************************************************************************
  * @file    adc.c
  * @brief   This file provides code for the configuration
  *          of the ADC instances.
  ******************************************************************************
  * @attention
  *
  * Copyright (c) 2025 STMicroelectronics.
  * All rights reserved.
  *
  * This software is licensed under terms that can be found in the LICENSE file
  * in the root directory of this software component.
  * If no LICENSE file comes with this software, it is provided AS-IS.
  *
  ******************************************************************************
  */
/* USER CODE END Header */
/* Includes ------------------------------------------------------------------*/
#include "adc.h"

/* USER CODE BEGIN 0 */

/* USER CODE END 0 */

ADC_HandleTypeDef hadc3;

/* ADC3 init function */
void MX_ADC3_Init(void)
{

  /* USER CODE BEGIN ADC3_Init 0 */

  /* USER CODE END ADC3_Init 0 */

  ADC_ChannelConfTypeDef sConfig = {0};

  /* USER CODE BEGIN ADC3_Init 1 */

  /* USER CODE END ADC3_Init 1 */

  /** Configure the global features of the ADC (Clock, Resolution, Data Alignment and number of conversion)
  */
  hadc3.Instance = ADC3;
  hadc3.Init.ClockPrescaler = ADC_CLOCK_SYNC_PCLK_DIV4;
  hadc3.Init.Resolution = ADC_RESOLUTION_12B;
  hadc3.Init.ScanConvMode = DISABLE;
  hadc3.Init.ContinuousConvMode = DISABLE;
  hadc3.Init.DiscontinuousConvMode = DISABLE;
  hadc3.Init.ExternalTrigConvEdge = ADC_EXTERNALTRIGCONVEDGE_NONE;
  hadc3.Init.ExternalTrigConv = ADC_SOFTWARE_START;
  hadc3.Init.DataAlign = ADC_DATAALIGN_RIGHT;
  hadc3.Init.NbrOfConversion = 1;
  hadc3.Init.DMAContinuousRequests = DISABLE;
  hadc3.Init.EOCSelection = ADC_EOC_SINGLE_CONV;
  if (HAL_ADC_Init(&hadc3) != HAL_OK)
  {
    Error_Handler();
  }

  /** Configure for the selected ADC regular channel its corresponding rank in the sequencer and its sample time.
  */
  sConfig.Channel = ADC_CHANNEL_4;
  sConfig.Rank = 1;
  sConfig.SamplingTime = ADC_SAMPLETIME_3CYCLES;
  if (HAL_ADC_ConfigChannel(&hadc3, &sConfig) != HAL_OK)
  {
    Error_Handler();
  }
  /* USER CODE BEGIN ADC3_Init 2 */

  /* USER CODE END ADC3_Init 2 */

}

void HAL_ADC_MspInit(ADC_HandleTypeDef* adcHandle)
{

  GPIO_InitTypeDef GPIO_InitStruct = {0};
  if(adcHandle->Instance==ADC3)
  {
  /* USER CODE BEGIN ADC3_MspInit 0 */

  /* USER CODE END ADC3_MspInit 0 */
    /* ADC3 clock enable */
    __HAL_RCC_ADC3_CLK_ENABLE();

    __HAL_RCC_GPIOF_CLK_ENABLE();
    __HAL_RCC_GPIOC_CLK_ENABLE();
    /**ADC3 GPIO Configuration
    PF6     ------> ADC3_IN4
    PF7     ------> ADC3_IN5
    PF8     ------> ADC3_IN6
    PF9     ------> ADC3_IN7
    PF10     ------> ADC3_IN8
    PC1     ------> ADC3_IN11
    PC2     ------> ADC3_IN12
    */
    GPIO_InitStruct.Pin = GPIO_PIN_6|GPIO_PIN_7|GPIO_PIN_8|GPIO_PIN_9
                          |GPIO_PIN_10;
    GPIO_InitStruct.Mode = GPIO_MODE_ANALOG;
    GPIO_InitStruct.Pull = GPIO_NOPULL;
    HAL_GPIO_Init(GPIOF, &GPIO_InitStruct);

    GPIO_InitStruct.Pin = GPIO_PIN_1|GPIO_PIN_2;
    GPIO_InitStruct.Mode = GPIO_MODE_ANALOG;
    GPIO_InitStruct.Pull = GPIO_NOPULL;
    HAL_GPIO_Init(GPIOC, &GPIO_InitStruct);

  /* USER CODE BEGIN ADC3_MspInit 1 */

  /* USER CODE END ADC3_MspInit 1 */
  }
}

void HAL_ADC_MspDeInit(ADC_HandleTypeDef* adcHandle)
{

  if(adcHandle->Instance==ADC3)
  {
  /* USER CODE BEGIN ADC3_MspDeInit 0 */

  /* USER CODE END ADC3_MspDeInit 0 */
    /* Peripheral clock disable */
    __HAL_RCC_ADC3_CLK_DISABLE();

    /**ADC3 GPIO Configuration
    PF6     ------> ADC3_IN4
    PF7     ------> ADC3_IN5
    PF8     ------> ADC3_IN6
    PF9     ------> ADC3_IN7
    PF10     ------> ADC3_IN8
    PC1     ------> ADC3_IN11
    PC2     ------> ADC3_IN12
    */
    HAL_GPIO_DeInit(GPIOF, GPIO_PIN_6|GPIO_PIN_7|GPIO_PIN_8|GPIO_PIN_9
                          |GPIO_PIN_10);

    HAL_GPIO_DeInit(GPIOC, GPIO_PIN_1|GPIO_PIN_2);

  /* USER CODE BEGIN ADC3_MspDeInit 1 */

  /* USER CODE END ADC3_MspDeInit 1 */
  }
}

/* USER CODE BEGIN 1 */

/* USER CODE END 1 */

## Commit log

2024-02-26 added kicad library
2024-02-26 started the project
2024-03-04 Tests
2024-03-04 1st attempt at routing the SDRAM
2024-03-05 routing 1st version
2024-03-06 silkscreen
2024-03-06 silkscreen again
2024-03-07 gnd vias
2024-03-12 Change SGTL5000 model due to obsolescence
2024-03-29 fabrication files
2024-03-29 added JLCJLCJLCJLC
2024-03-29 solder paste clearance 10%
2025-10-10 carryer board for dsp som
2025-10-11 routing carry board
2025-10-12 carry board silkscreen
2025-10-13 bringup
2025-10-13 fab files for carry board
2025-10-14 changed SAI frequency to make SGTL5000 work
2025-10-14 Continuing bringup
2025-10-14 sd card OK
2025-10-24 CODEC OK!
2025-11-05 test display with carry board
2025-11-05 3d models
2025-11-06 coder
2025-11-06 parameters
2025-11-07 sd card parameters memorization
2025-11-07 sgtl5000 driver not tested
2025-11-09 vumeter
2025-11-09 TODO list
2025-11-10 added mono/stereo + cpu stats
2025-11-10 delay attempt
2025-11-10 added clipping drama
2025-11-10 sd still don't work
2025-11-12 SD DMA with audio OK
2025-11-12 preparing for tinywav
2025-11-12 added tinywav
2025-11-13 audio playback not tested
2025-11-13 playback OK (if display is deactivated)
2025-11-13 Playback + Display with freertos
2025-11-14 added i2c dma to ssd1306
2025-11-14 added an old grnlr untested code
2025-11-14 added a very old grnlr code, not complete, not tested
2025-11-14 debuging grnlr
2025-11-19 minor corrections
2025-11-19 tests opti
2025-11-20 parameters reorganisation
2025-11-20 gcc -O2 + started reconding grnlr
2025-11-21 first working(ish) version of grnlr
2025-11-21 vscode stuff
2025-11-21 removed useless (for now) params
2025-11-21 oups forgot a modulo
2025-11-24 added feedback
